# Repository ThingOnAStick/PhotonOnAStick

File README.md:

# PhotonOnAStick
Various prototype boards for the Particle Photon on a USB Stick style.

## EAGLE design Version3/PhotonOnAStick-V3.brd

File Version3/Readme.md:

Photon On A Stick - V3
-----------------------------

Standard format prototype board for Particle Photon.

Features:
=========

* USB power in via A Connector on left edge or B Connector on Photon. Do not connect both at once.
* Pull-up or down 1206 pads on A0-A7. Suitable for 1206 or 0805 components.
* Two 1206 in series to GND on D0-D7. Suitable for 1206 or 0805 components. Use for LED + resistor, Resistor + Capacitor, Resistor + Resistor (or 0R) pull down.
* LED/Resistor/Capacitor 1206 pads Right edge along with 8x2 header for off board connection (8 pins to 1206's and 8 GND. Top 1206 connected to nearest pin, bottom 1206 to 1 in pin.
* 4 1206 pads top/bottom by end of Photon connected to pins to the right of the pad. Ideal of Capacitors, Resistor or LED.
* 3 Mounting holes to allow board to be mounted in case for final use.
* 2 SOT-23 FET/Transistor under Photon with Gate/Base guard and pull down resistor options.

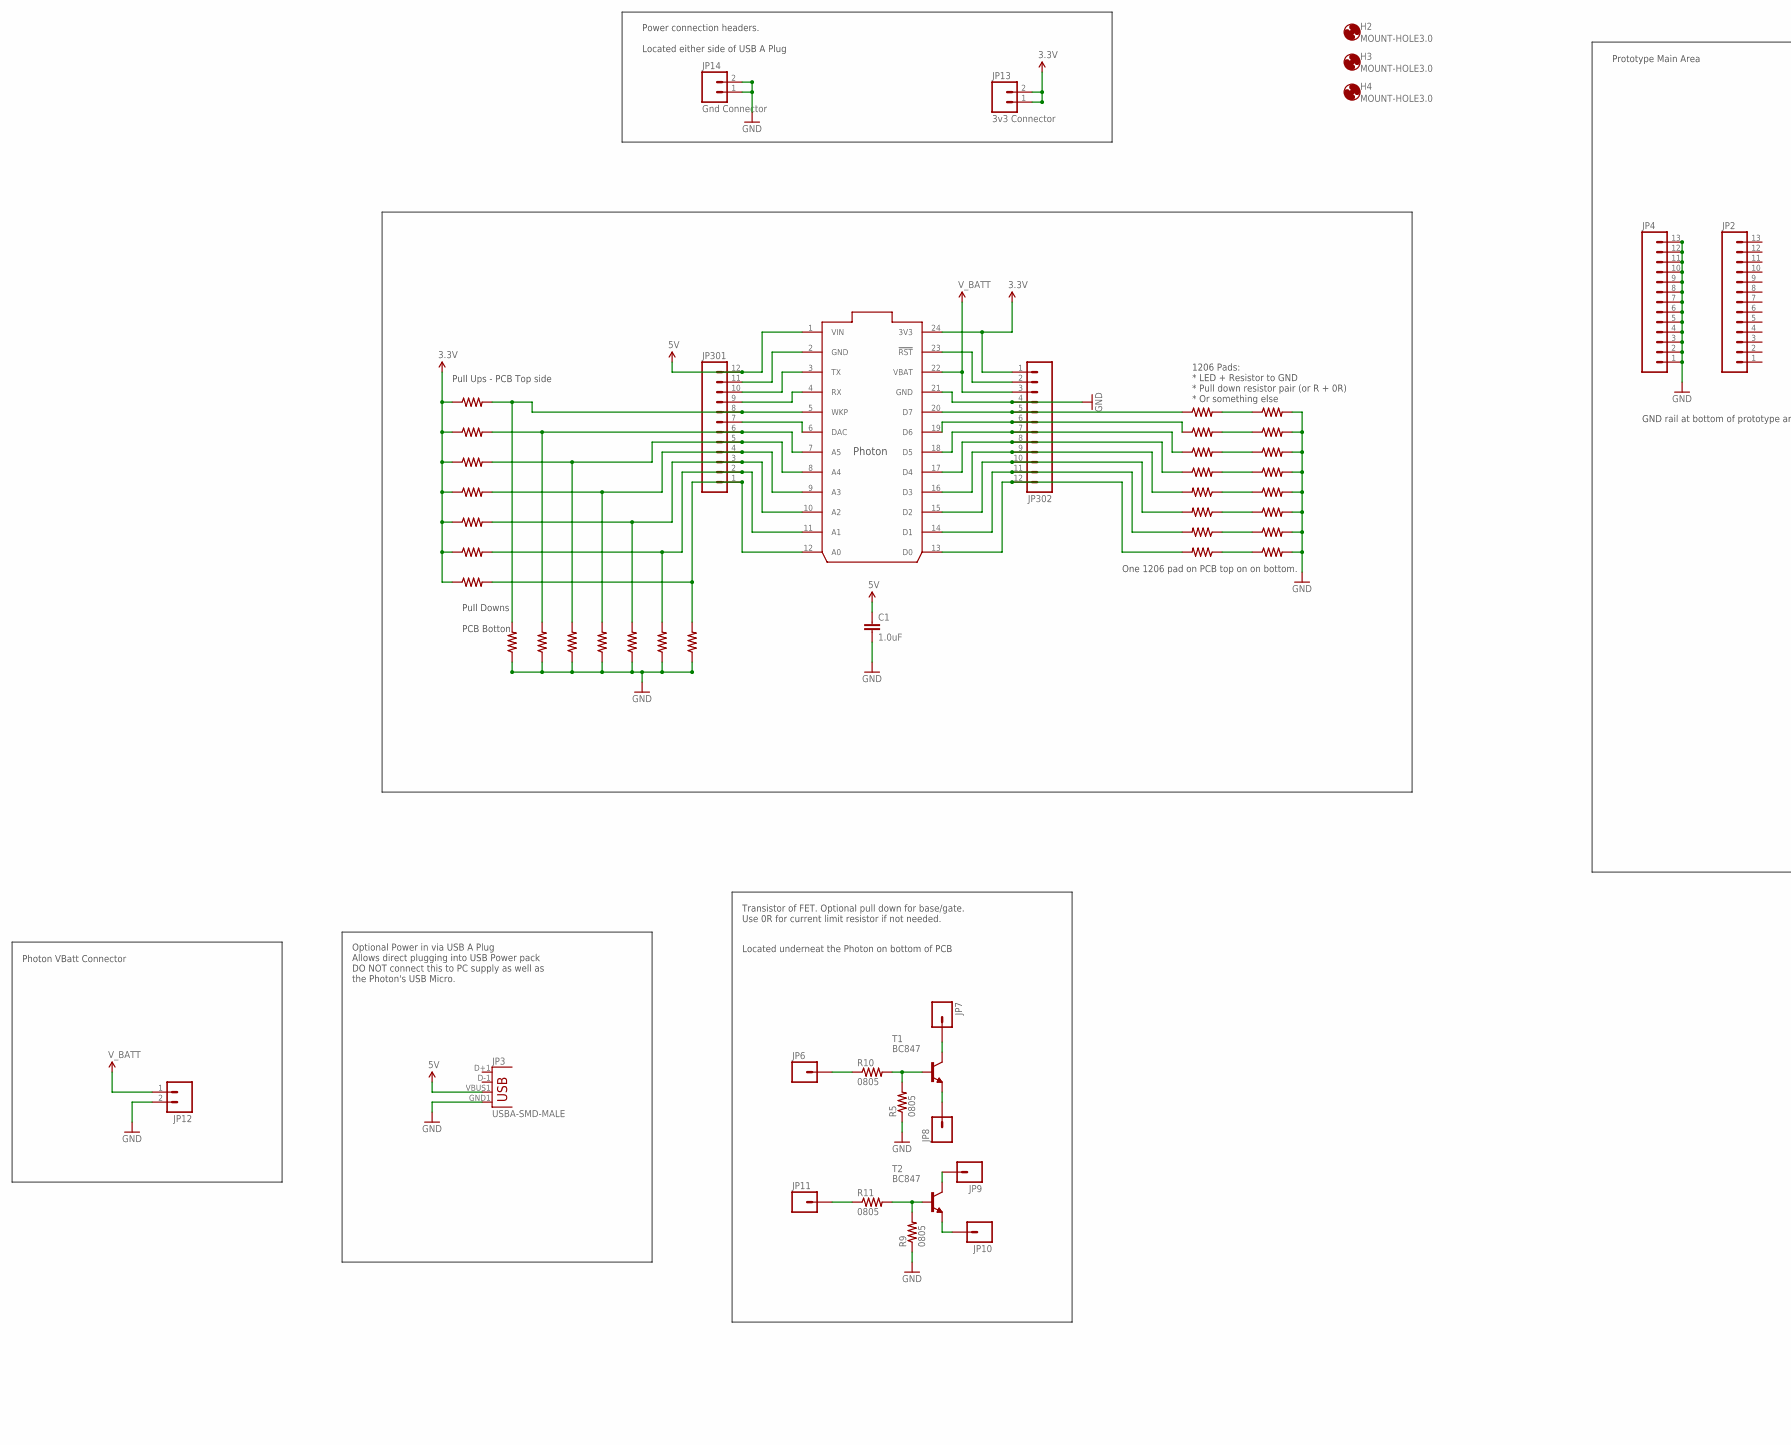
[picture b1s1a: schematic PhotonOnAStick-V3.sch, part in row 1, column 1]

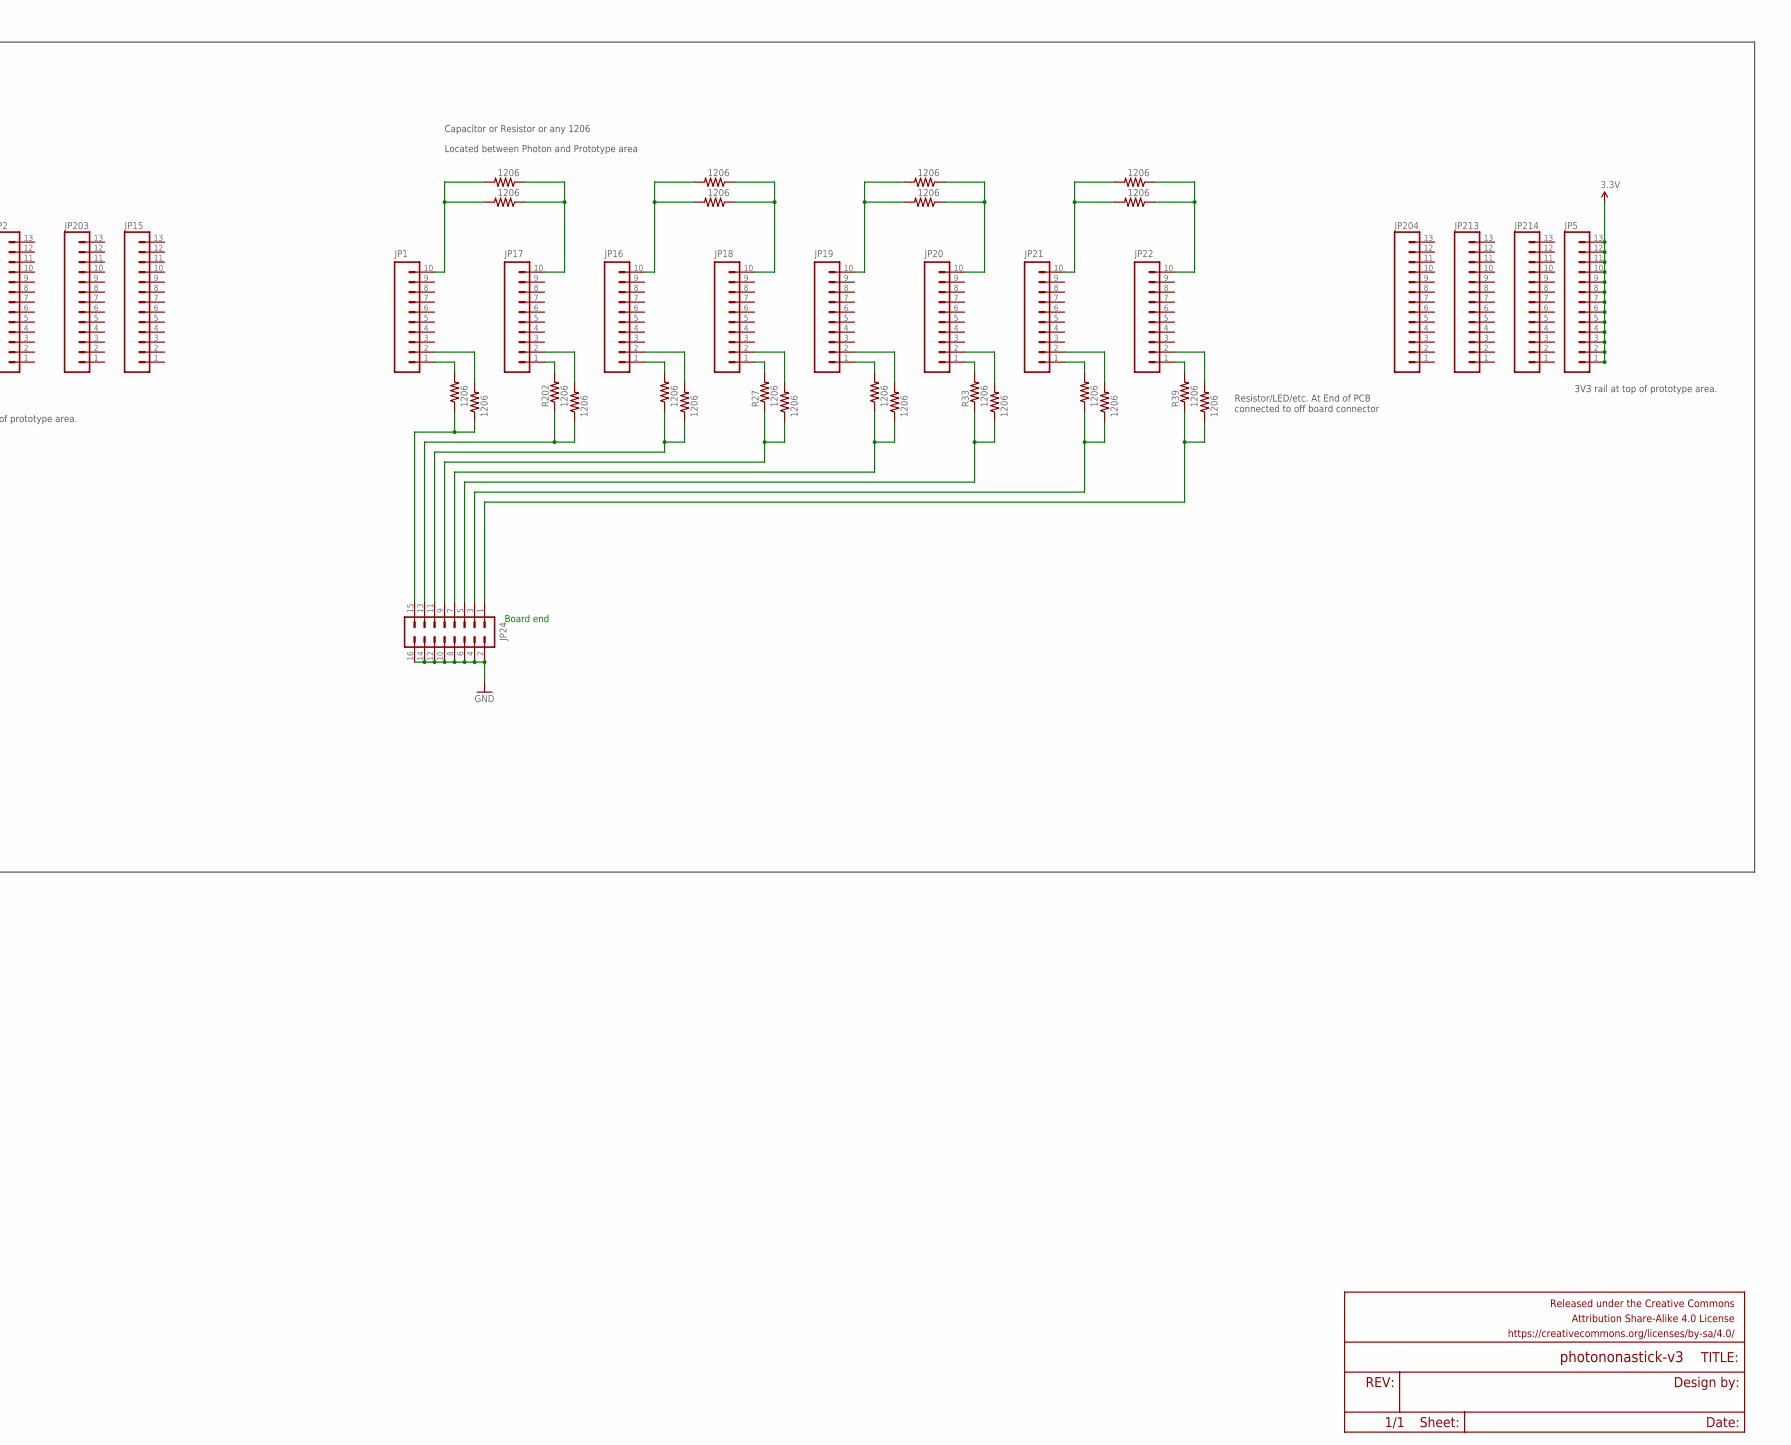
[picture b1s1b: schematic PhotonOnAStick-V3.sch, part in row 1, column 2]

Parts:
C1: 1.0uF; 0805-CAP
FRAME1: FRAME-LEDGER; CREATIVE_COMMONS
H2, H3, H4: MOUNT-HOLE3.0; 3,0
IC1: PHOTON_WITH_HEADERS; PHOTON
JP1, JP16, JP17, JP18, JP19, JP20, JP21, JP22: M10SILK_FEMALE_PTH; 1X10
JP2, JP4, JP5, JP15, JP203, JP204, JP213, JP214: M13; 1X13
JP3: USBA-SMD-MALE; USB-A-SMT-MALE
JP6, JP7, JP8, JP9, JP10, JP11: M01PTH; 1X01
JP12: M02JST-PTH-2; JST-2-PTH
JP13: 3v3 Connector; 1X02
JP14: Gnd Connector; 1X02
JP24: M08X2; 2X8
JP301, JP302: M12PTH; 1X12
R1, R2, R3, R4, R6, R7, R8, R12, R13, R14, R15, R16, R17, R18, R19, R20, R21, R22, R23, R24, R25, R26, R27, R28, R29, R30, R31, R32, R33, R34, R35, R36, R37, R38, R39, R40, R41, R42, R43, R44, R201, R202, R313, R314, R315, R316, R317, R318, R319, R320, R410, R411, R412, R413: 1206
R5, R9, R10, R11: 0805
T1, T2: BC847; SOT23

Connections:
3.3V: IC1.24 (3V3), JP5.1, JP5.2, JP5.3, JP5.4, JP5.5, JP5.6, JP5.7, JP5.8, JP5.9, JP5.10, JP5.11, JP5.12, JP5.13, JP13.1, JP13.2, JP302.1, R1.1, R2.1, R3.1, R4.1, R6.1, R7.1, R12.1
5V: C1.1, IC1.1 (VIN), JP3.VBUS1 (VBUS), JP301.12
GND: C1.2, IC1.2 (GND), IC1.21 (GND), JP3.GND1 (GND), JP4.1, JP4.2, JP4.3, JP4.4, JP4.5, JP4.6, JP4.7, JP4.8, JP4.9, JP4.10, JP4.11, JP4.12, JP4.13, JP12.2, JP14.1, JP14.2, JP24.2, JP24.4, JP24.6, JP24.8, JP24.10, JP24.12, JP24.14, JP24.16, JP301.11, JP302.4, R5.1, R8.1, R9.1, R13.1, R14.1, R15.2, R16.2, R17.2, R18.2, R19.1, R20.1, R21.1, R22.1, R410.2, R411.2, R412.2, R413.2
unnamed: JP6.1, R10.1
unnamed: JP17.1, R202.2
unnamed: JP1.1, R201.2
unnamed: IC1.3 (TX), JP301.10
unnamed: IC1.4 (RX), JP301.9
unnamed: IC1.5 (WKP), JP301.8, R8.2, R12.2
unnamed: IC1.6 (DAC), JP301.7
unnamed: IC1.7 (A5), JP301.6, R1.2, R13.2
unnamed: IC1.8 (A4), JP301.5, R2.2, R14.2
unnamed: IC1.9 (A3), JP301.4, R3.2, R19.2
unnamed: IC1.10 (A2), JP301.3, R4.2, R20.2
unnamed: IC1.11 (A1), JP301.2, R6.2, R21.2
unnamed: IC1.12 (A0), JP301.1, R7.2, R22.2
unnamed: JP24.15, R23.1, R201.1
unnamed: R5.2, R10.2, T1.1 (B)
unnamed: IC1.18 (D5), JP302.7, R318.1
unnamed: IC1.17 (D4), JP302.8, R317.1
unnamed: IC1.16 (D3), JP302.9, R316.2
unnamed: IC1.15 (D2), JP302.10, R315.2
unnamed: IC1.14 (D1), JP302.11, R314.2
unnamed: IC1.13 (D0), JP302.12, R313.2
unnamed: JP1.2, R23.2
unnamed: JP1.10, R24.2, R25.2
unnamed: IC1.23 (!RST), JP302.2
unnamed: R320.2, R410.1
unnamed: JP17.10, R24.1, R25.1
unnamed: JP17.2, R26.2
unnamed: JP24.13, R26.1, R202.1
unnamed: JP18.1, R27.2
unnamed: JP16.1, R28.2
unnamed: JP24.11, R28.1, R29.1
unnamed: JP16.2, R29.2
unnamed: JP16.10, R30.2, R31.2
unnamed: JP18.10, R30.1, R31.1
unnamed: JP18.2, R32.2
unnamed: JP24.9, R27.1, R32.1
unnamed: JP20.1, R33.2
unnamed: IC1.20 (D7), JP302.5, R320.1
unnamed: IC1.19 (D6), JP302.6, R319.1
unnamed: JP19.1, R34.2
unnamed: JP7.1, T1.3 (C)
unnamed: JP24.7, R34.1, R35.1
unnamed: R18.1, R313.1
unnamed: R17.1, R314.1
unnamed: R16.1, R315.1
unnamed: R15.1, R316.1
unnamed: R317.2, R413.1
unnamed: R318.2, R412.1
unnamed: R319.2, R411.1
unnamed: JP19.2, R35.2
unnamed: JP19.10, R36.2, R37.2
unnamed: JP20.10, R36.1, R37.1
unnamed: JP8.1, T1.2 (E)
unnamed: JP20.2, R38.2
unnamed: JP24.5, R33.1, R38.1
unnamed: JP22.1, R39.2
unnamed: JP11.1, R11.1
unnamed: R9.2, R11.2, T2.1 (B)
unnamed: JP9.1, T2.3 (C)
unnamed: JP10.1, T2.2 (E)
unnamed: JP21.1, R40.2
unnamed: JP24.3, R40.1, R41.1
unnamed: JP21.2, R41.2
unnamed: JP21.10, R42.2, R43.2
unnamed: JP22.10, R42.1, R43.1
unnamed: JP22.2, R44.2
unnamed: JP24.1, R39.1, R44.1
V_BATT: IC1.22 (VBAT), JP12.1, JP302.3

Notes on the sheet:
Prototype Main Area
Board end
1206 Pads: * LED + Resistor to GND * Pull down resistor pair (or R + 0R) * Or something else
Pull Ups - PCB Top side
Pull Downs PCB Botton
Capacitor or Resistor or any 1206
Located between Photon and Prototype area
Resistor/LED/etc. At End of PCB connected to off board connector
Transistor of FET. Optional pull down for base/gate. Use 0R for current limit resistor if not needed.
Located underneat the Photon on bottom of PCB
Optional Power in via USB A Plug Allows direct plugging into USB Power pack DO NOT connect this to PC supply as well as the Photon's USB Micro.
Photon VBatt Connector
Power connection headers. Located either side of USB A Plug
One 1206 pad on PCB top on on bottom.
GND rail at bottom of prototype area.
3V3 rail at top of prototype area.

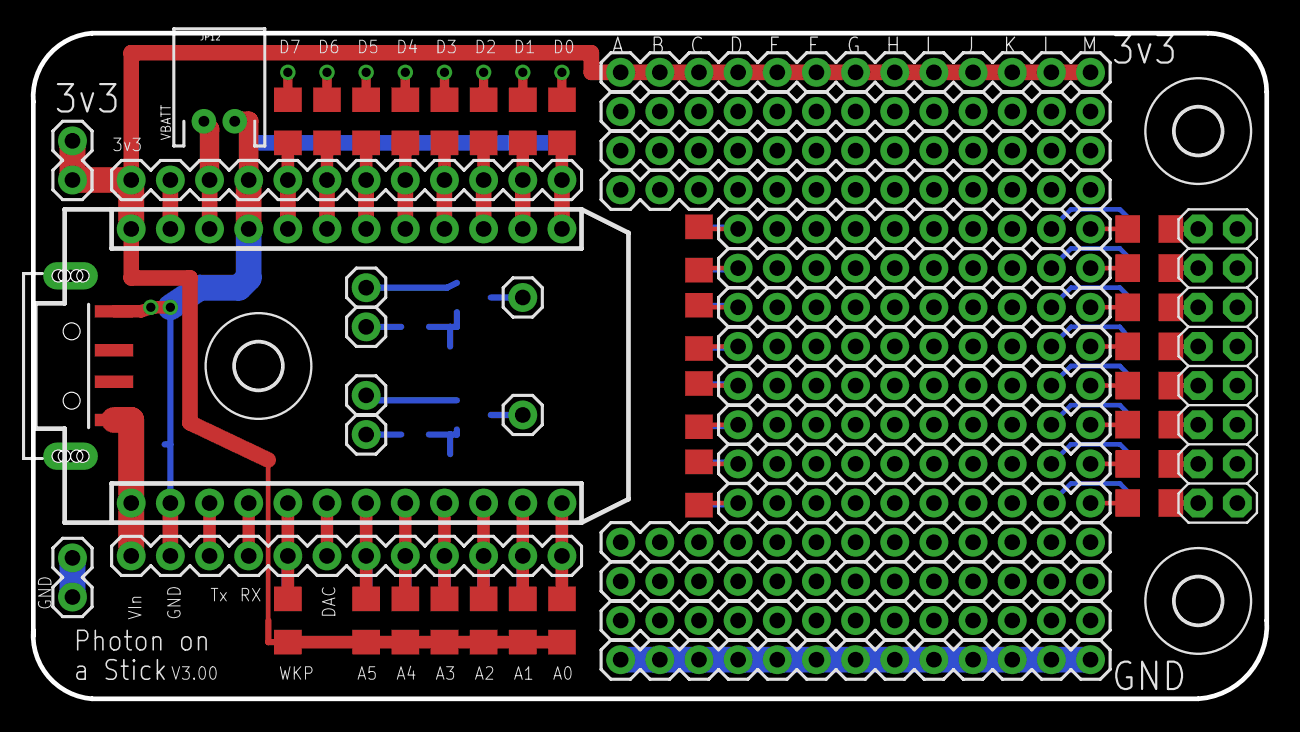
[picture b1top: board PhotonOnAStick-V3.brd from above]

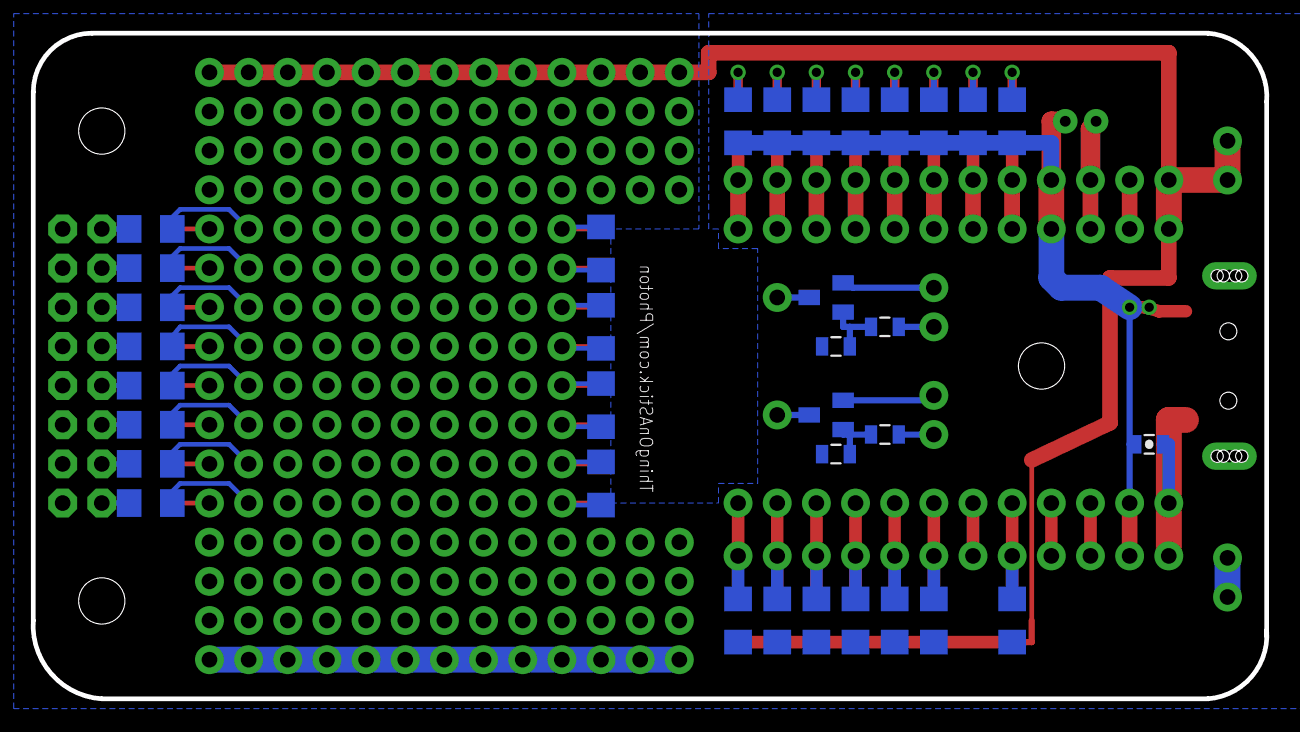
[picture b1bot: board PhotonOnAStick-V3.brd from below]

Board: 2 copper layers, 80.0 x 43.2 mm, 95 parts (34 on the bottom side), 71 nets.

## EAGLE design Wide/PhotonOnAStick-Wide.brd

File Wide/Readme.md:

Photon On A Stick - Wide - V4
-----------------------------

Wide format prototype board for Particle Photon.

Features:
=========

* USB power in via A Connector on left edge.
* Battery power in via JST under Photon. Do not use at the same time as power in via USB A or Photon USB.
* Pull-up or down 1206 pads on D0-D7 and A0-A7. Suitable for 1206 or 0805 components.
* LED/Resistor/Capacitor 1206 pads along top edge, along both top and bottom or board (although you probably don't want both at once!)
* 4 mounting holes to allow board to be mounted in case for final use.

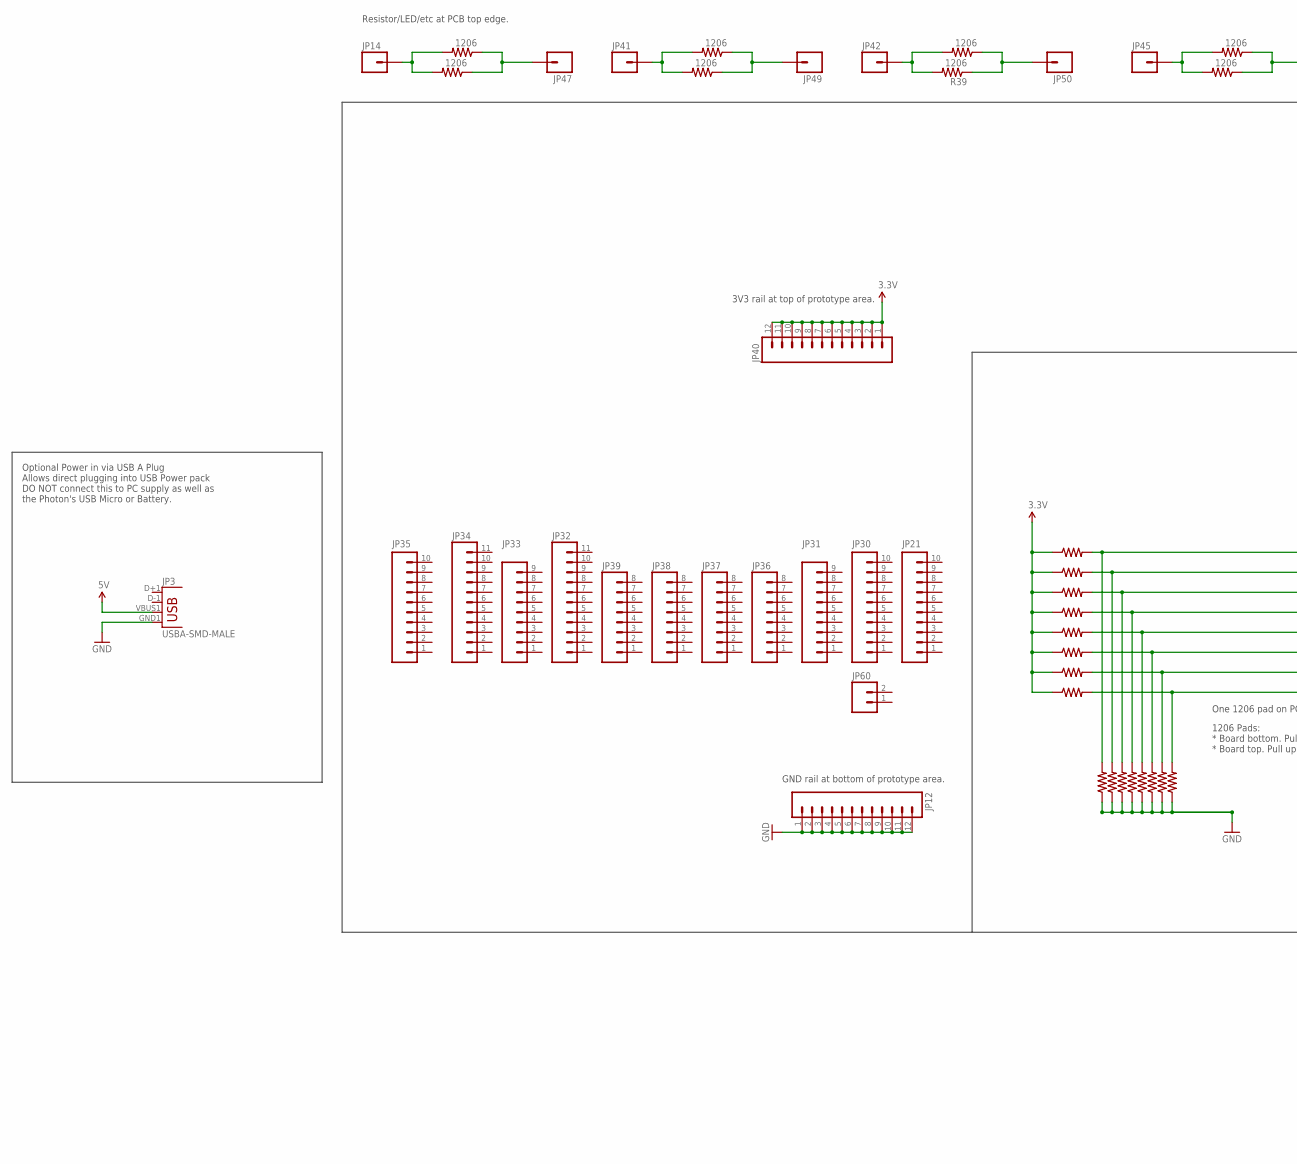
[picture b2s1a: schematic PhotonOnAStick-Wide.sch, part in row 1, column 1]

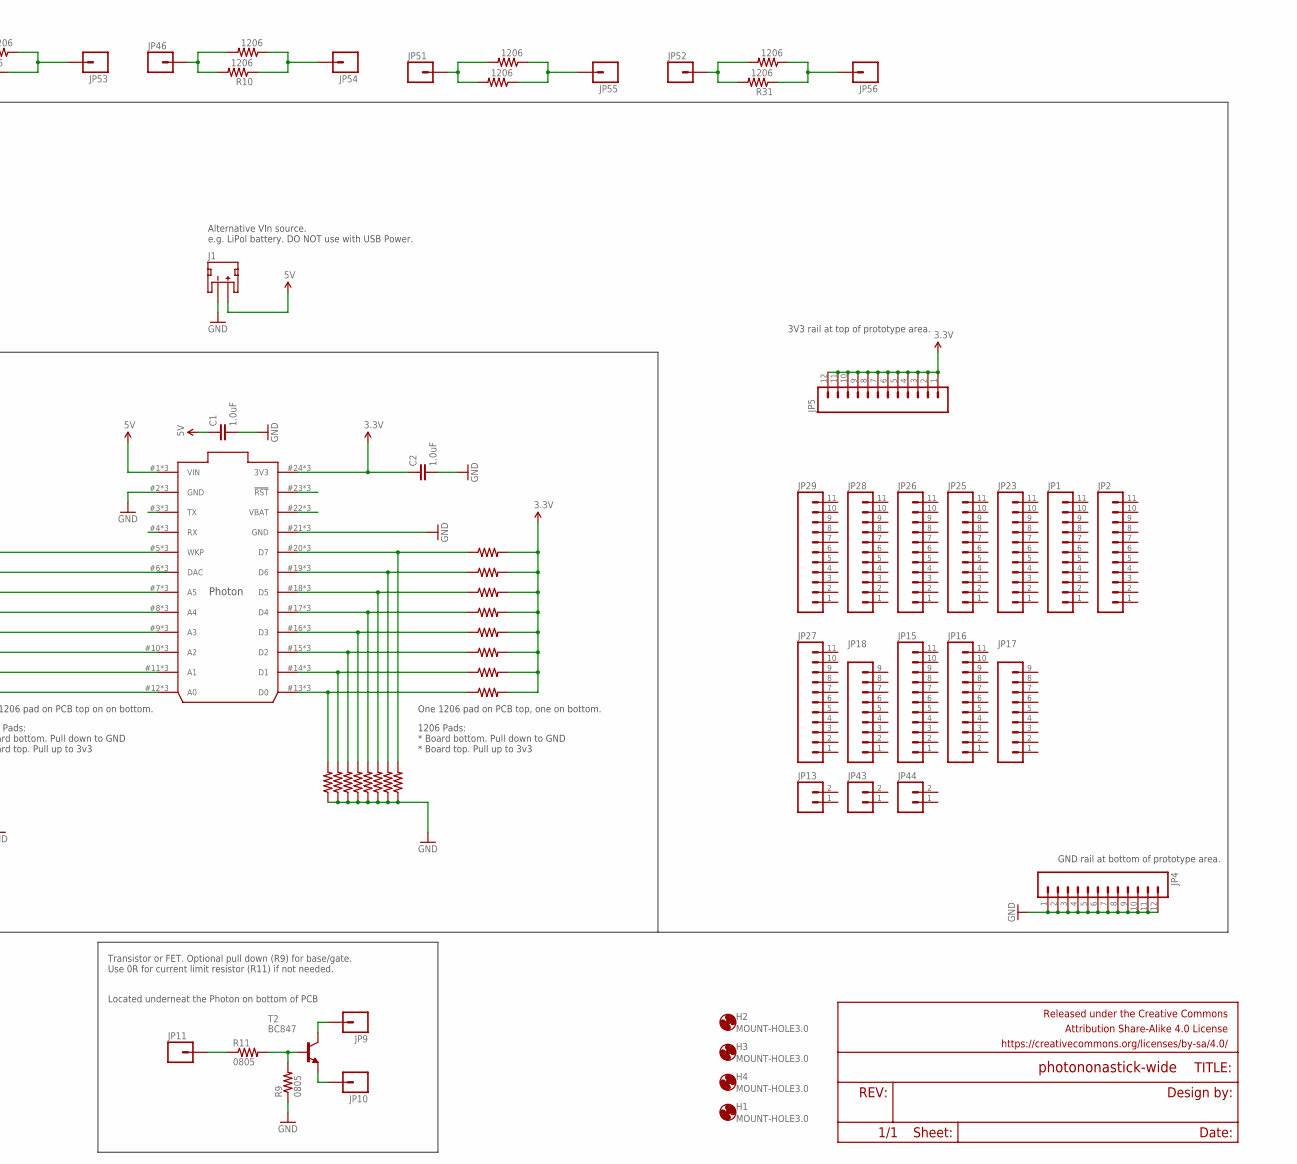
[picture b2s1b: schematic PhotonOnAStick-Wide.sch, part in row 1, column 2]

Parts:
C1, C2: 1.0uF; 0805-CAP
FRAME1: FRAME-LEDGER; CREATIVE_COMMONS
H1, H2, H3, H4: MOUNT-HOLE3.0; 3,0
IC1: PHOTON_WITH_STACKABLE_HEADERS; PHOTON_STACKABLE
J1: JST_2MM_MALE; JST-2-SMD
JP1, JP2, JP15, JP16, JP23, JP25, JP26, JP27, JP28, JP29, JP32, JP34: M111X11_NO_SILK; 1X11_NO_SILK
JP3: USBA-SMD-MALE; USB-A-SMT-MALE
JP4, JP5, JP12, JP40: M12PTH; 1X12
JP9, JP10, JP11, JP14, JP41, JP42, JP45, JP46, JP47, JP49, JP50, JP51, JP52, JP53, JP54, JP55, JP56: M01PTH; 1X01
JP13, JP43, JP44, JP60: M021X02_NO_SILK; 1X02_NO_SILK
JP17, JP18, JP31, JP33: M09NO_SILK; 1X09_NO_SILK
JP21, JP30, JP35: M10NO_SILK_PTH_FEMALE; 1X10_NO_SILK
JP36, JP37, JP38, JP39: M08NO_SILK_FEMALE_PTH; 1X08_NO_SILK
R1, R2, R3, R4, R5, R6, R7, R8, R10, R12, R13, R14, R15, R16, R17, R18, R19, R20, R21, R22, R23, R24, R25, R26, R27, R28, R29, R30, R31, R32, R34, R35, R36, R37, R39, R40, R41, R42, R43, R44, R45, R46, R47, R48, R49, R50: 1206
R9, R11: 0805
T2: BC847; SOT23

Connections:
3.3V: C2.1, IC1.24 (3V3), IC1.#24 (3V3), IC1.@24 (3V3), JP5.1, JP5.2, JP5.3, JP5.4, JP5.5, JP5.6, JP5.7, JP5.8, JP5.9, JP5.10, JP5.11, JP5.12, JP40.1, JP40.2, JP40.3, JP40.4, JP40.5, JP40.6, JP40.7, JP40.8, JP40.9, JP40.10, JP40.11, JP40.12, R1.1, R2.1, R3.1, R4.1, R5.2, R6.1, R7.1, R12.1, R15.1, R18.2, R23.2, R25.2, R26.2, R27.2, R28.2, R29.2
5V: C1.1, IC1.1 (VIN), IC1.#1 (VIN), IC1.@1 (VIN), J1.2 (+), JP3.VBUS1 (VBUS)
GND: C1.2, C2.2, IC1.2 (GND), IC1.21 (GND), IC1.#2 (GND), IC1.#21 (GND), IC1.@2 (GND), IC1.@21 (GND), J1.1 (-), JP3.GND1 (GND), JP4.1, JP4.2, JP4.3, JP4.4, JP4.5, JP4.6, JP4.7, JP4.8, JP4.9, JP4.10, JP4.11, JP4.12, JP12.1, JP12.2, JP12.3, JP12.4, JP12.5, JP12.6, JP12.7, JP12.8, JP12.9, JP12.10, JP12.11, JP12.12, R8.1, R9.1, R13.1, R14.1, R16.1, R19.1, R20.1, R21.1, R22.1, R42.1, R43.1, R45.1, R46.1, R47.1, R48.1, R49.1, R50.1
unnamed: JP42.1, R39.2, R44.2
unnamed: IC1.22 (VBAT), IC1.#22 (VBAT), IC1.@22 (VBAT)
unnamed: IC1.20 (D7), IC1.#20 (D7), IC1.@20 (D7), R5.1, R50.2
unnamed: JP53.1, R17.1, R24.1
unnamed: JP45.1, R17.2, R24.2
unnamed: IC1.5 (WKP), IC1.#5 (WKP), IC1.@5 (WKP), R8.2, R12.2
unnamed: IC1.6 (DAC), IC1.#6 (DAC), IC1.@6 (DAC), R15.2, R16.2
unnamed: IC1.7 (A5), IC1.#7 (A5), IC1.@7 (A5), R1.2, R13.2
unnamed: IC1.8 (A4), IC1.#8 (A4), IC1.@8 (A4), R2.2, R14.2
unnamed: IC1.9 (A3), IC1.#9 (A3), IC1.@9 (A3), R3.2, R19.2
unnamed: IC1.10 (A2), IC1.#10 (A2), IC1.@10 (A2), R4.2, R20.2
unnamed: IC1.11 (A1), IC1.#11 (A1), IC1.@11 (A1), R6.2, R21.2
unnamed: IC1.12 (A0), IC1.#12 (A0), IC1.@12 (A0), R7.2, R22.2
unnamed: IC1.19 (D6), IC1.#19 (D6), IC1.@19 (D6), R18.1, R49.2
unnamed: IC1.13 (D0), IC1.#13 (D0), IC1.@13 (D0), R26.1, R42.2
unnamed: IC1.14 (D1), IC1.#14 (D1), IC1.@14 (D1), R25.1, R43.2
unnamed: IC1.18 (D5), IC1.#18 (D5), IC1.@18 (D5), R23.1, R48.2
unnamed: IC1.17 (D4), IC1.#17 (D4), IC1.@17 (D4), R29.1, R47.2
unnamed: IC1.16 (D3), IC1.#16 (D3), IC1.@16 (D3), R28.1, R46.2
unnamed: IC1.15 (D2), IC1.#15 (D2), IC1.@15 (D2), R27.1, R45.2
unnamed: JP46.1, R10.2, R30.2
unnamed: JP54.1, R10.1, R30.1
unnamed: JP55.1, R32.1, R36.1
unnamed: JP51.1, R32.2, R36.2
unnamed: JP56.1, R31.1, R37.1
unnamed: JP52.1, R31.2, R37.2
unnamed: IC1.4 (RX), IC1.#4 (RX), IC1.@4 (RX)
unnamed: IC1.3 (TX), IC1.#3 (TX), IC1.@3 (TX)
unnamed: IC1.23 (!RST), IC1.#23 (!RST), IC1.@23 (!RST)
unnamed: JP47.1, R34.1, R35.1
unnamed: JP14.1, R34.2, R35.2
unnamed: JP11.1, R11.1
unnamed: R9.2, R11.2, T2.1 (B)
unnamed: JP9.1, T2.3 (C)
unnamed: JP10.1, T2.2 (E)
unnamed: JP49.1, R40.1, R41.1
unnamed: JP41.1, R40.2, R41.2
unnamed: JP50.1, R39.1, R44.1

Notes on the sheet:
1206 Pads: * Board bottom. Pull down to GND * Board top. Pull up to 3v3
Resistor/LED/etc at PCB top edge.
Transistor or FET. Optional pull down (R9) for base/gate. Use 0R for current limit resistor (R11) if not needed.
Located underneat the Photon on bottom of PCB
Optional Power in via USB A Plug Allows direct plugging into USB Power pack DO NOT connect this to PC supply as well as the Photon's USB Micro or Battery.
One 1206 pad on PCB top, one on bottom.
GND rail at bottom of prototype area.
3V3 rail at top of prototype area.
One 1206 pad on PCB top on on bottom.
Alternative VIn source. e.g. LiPol battery. DO NOT use with USB Power.

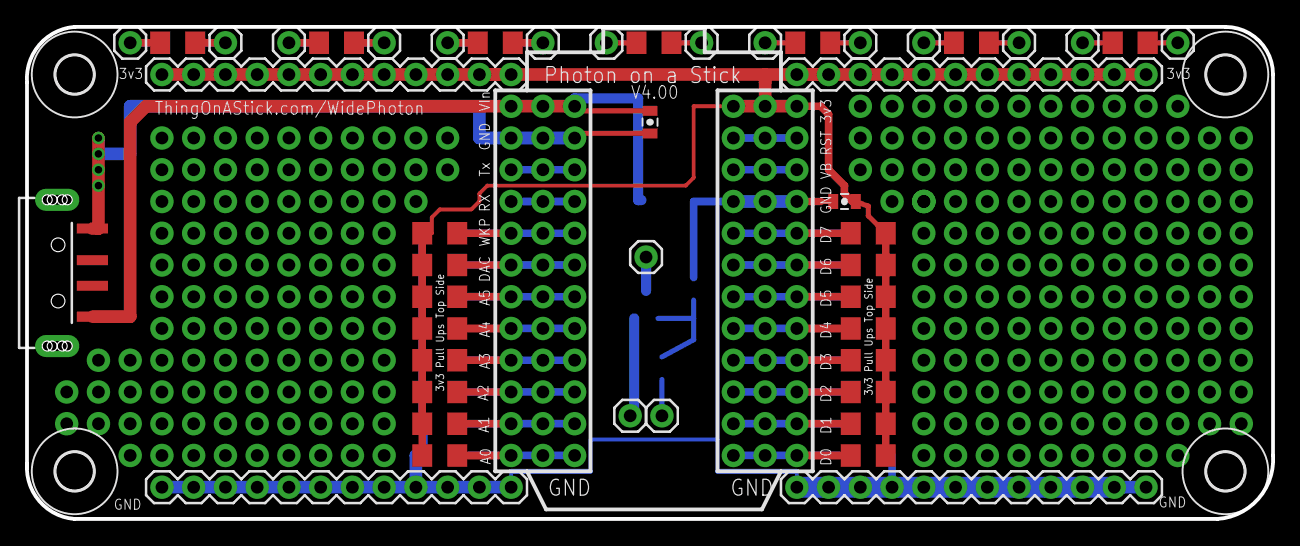
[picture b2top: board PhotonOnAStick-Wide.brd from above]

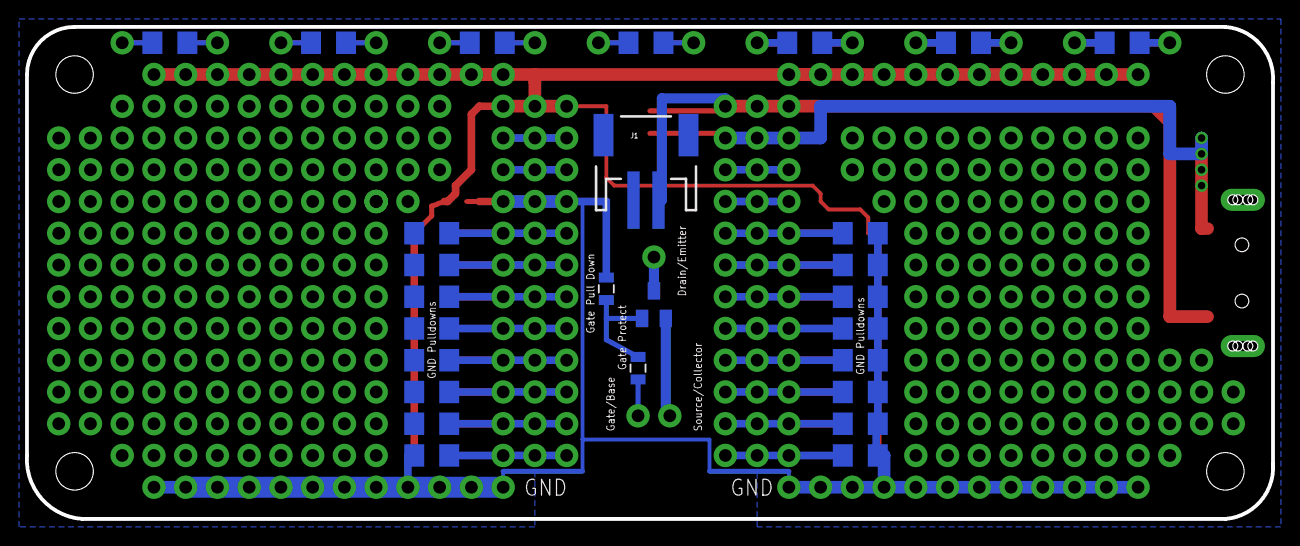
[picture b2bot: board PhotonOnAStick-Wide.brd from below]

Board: 2 copper layers, 99.7 x 39.4 mm, 107 parts (27 on the bottom side), 41 nets.

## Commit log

2015-12-06 Added wide (v4) version of PCB.
2015-12-14 Initial version of V3 board as sent to OSHPark
2016-11-18 Removed Wide Photon PCB to own repo

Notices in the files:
parts and their libraries:
SparkFun-Connectors: Licensing: Creative Commons ShareAlike 4.0 International - https://creativecommons.org/licenses/by-sa/4.0
SparkFun-Aesthetics: Released under the Creative Commons Attribution Share-Alike 4.0 License
SparkFun-Aesthetics: https://creativecommons.org/licenses/by-sa/4.0
